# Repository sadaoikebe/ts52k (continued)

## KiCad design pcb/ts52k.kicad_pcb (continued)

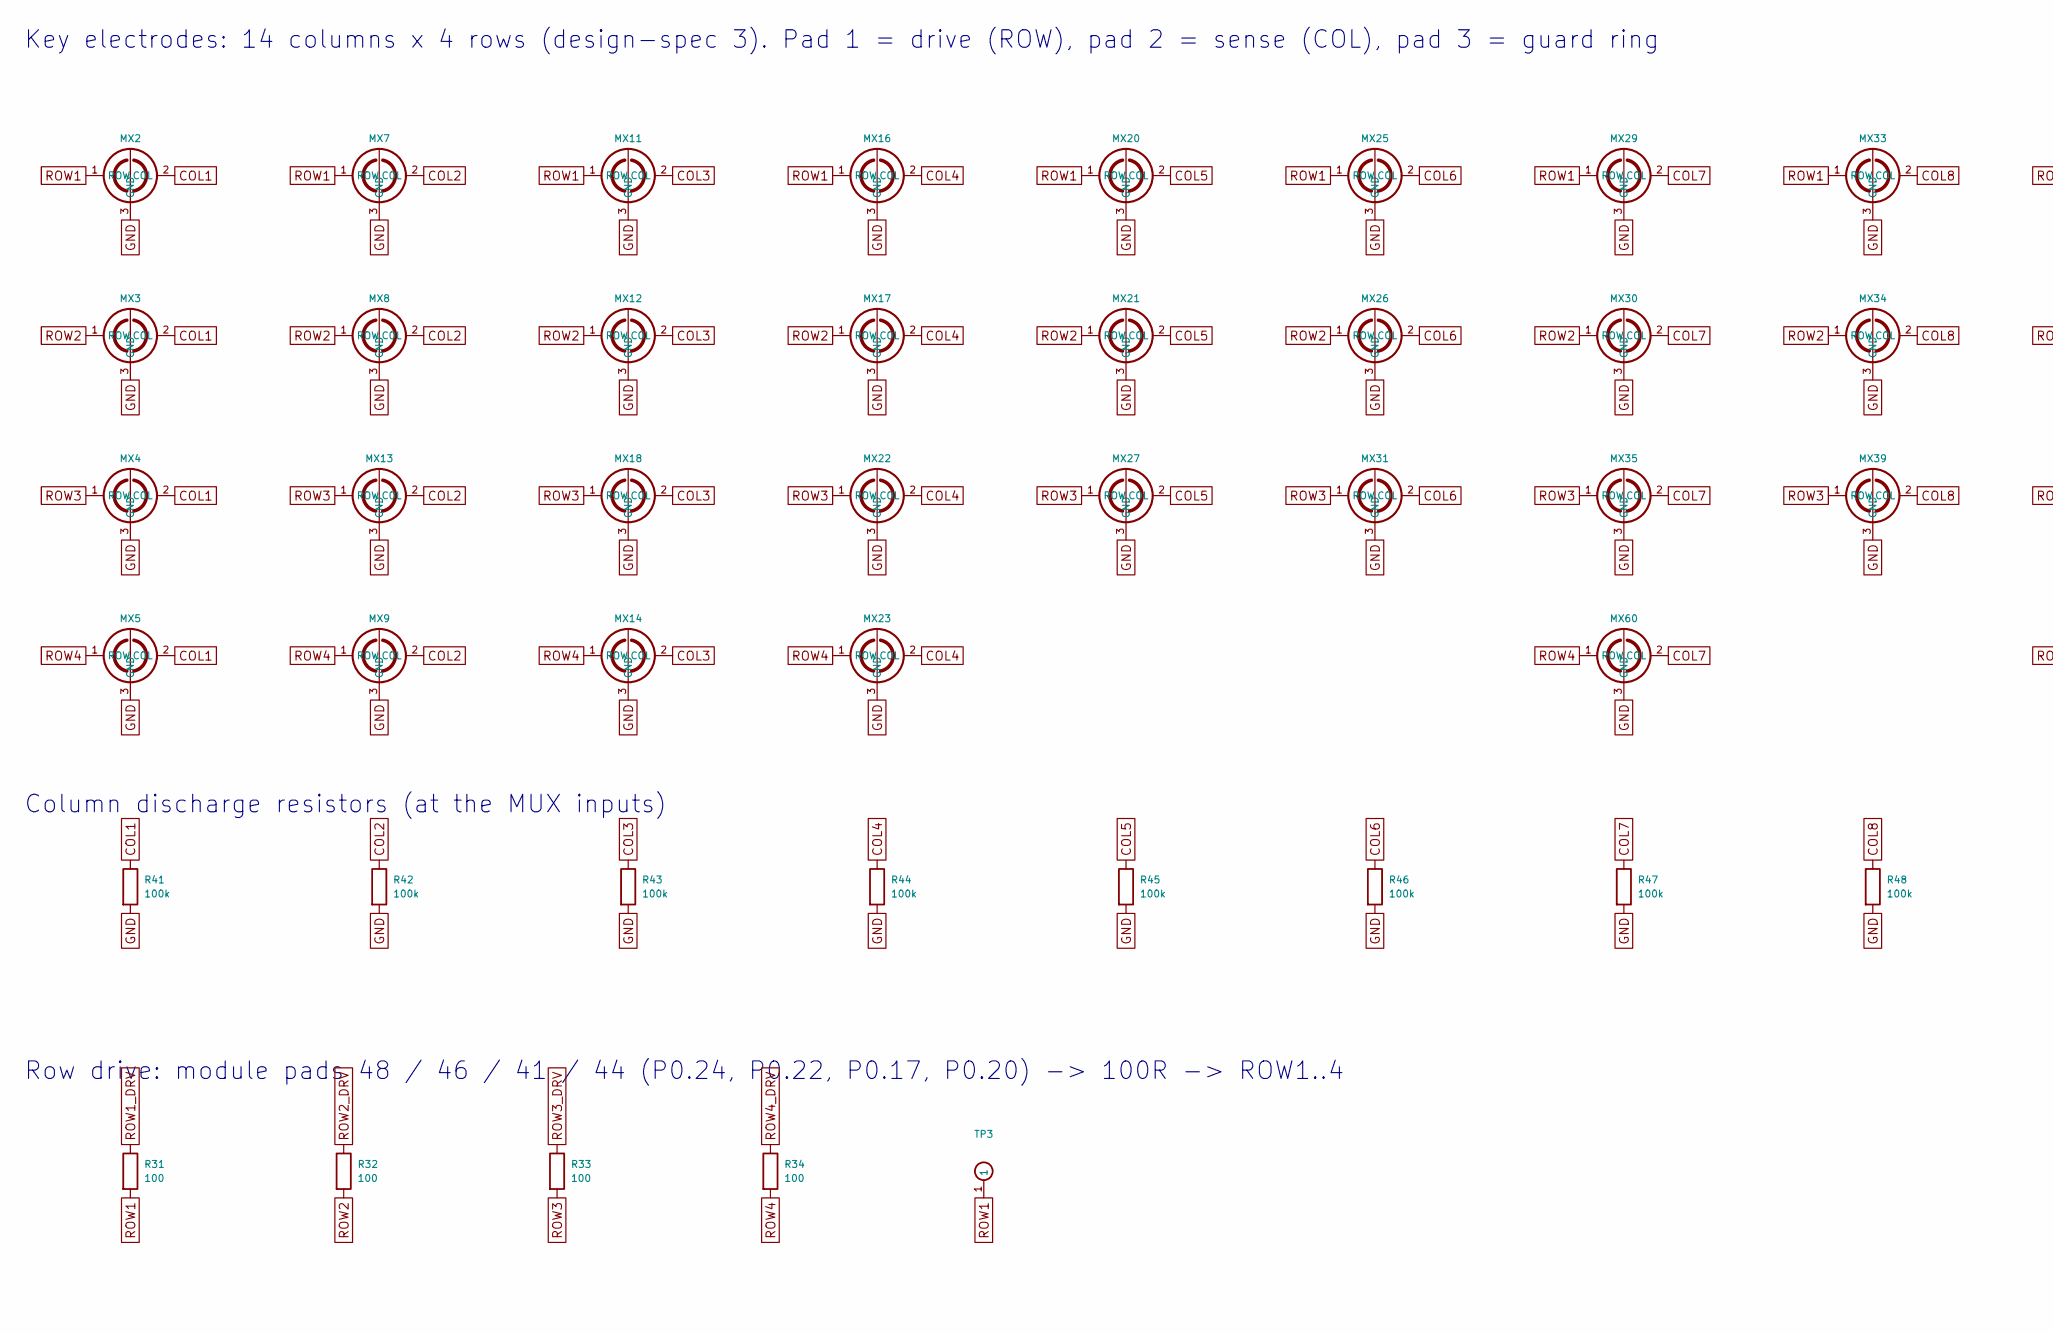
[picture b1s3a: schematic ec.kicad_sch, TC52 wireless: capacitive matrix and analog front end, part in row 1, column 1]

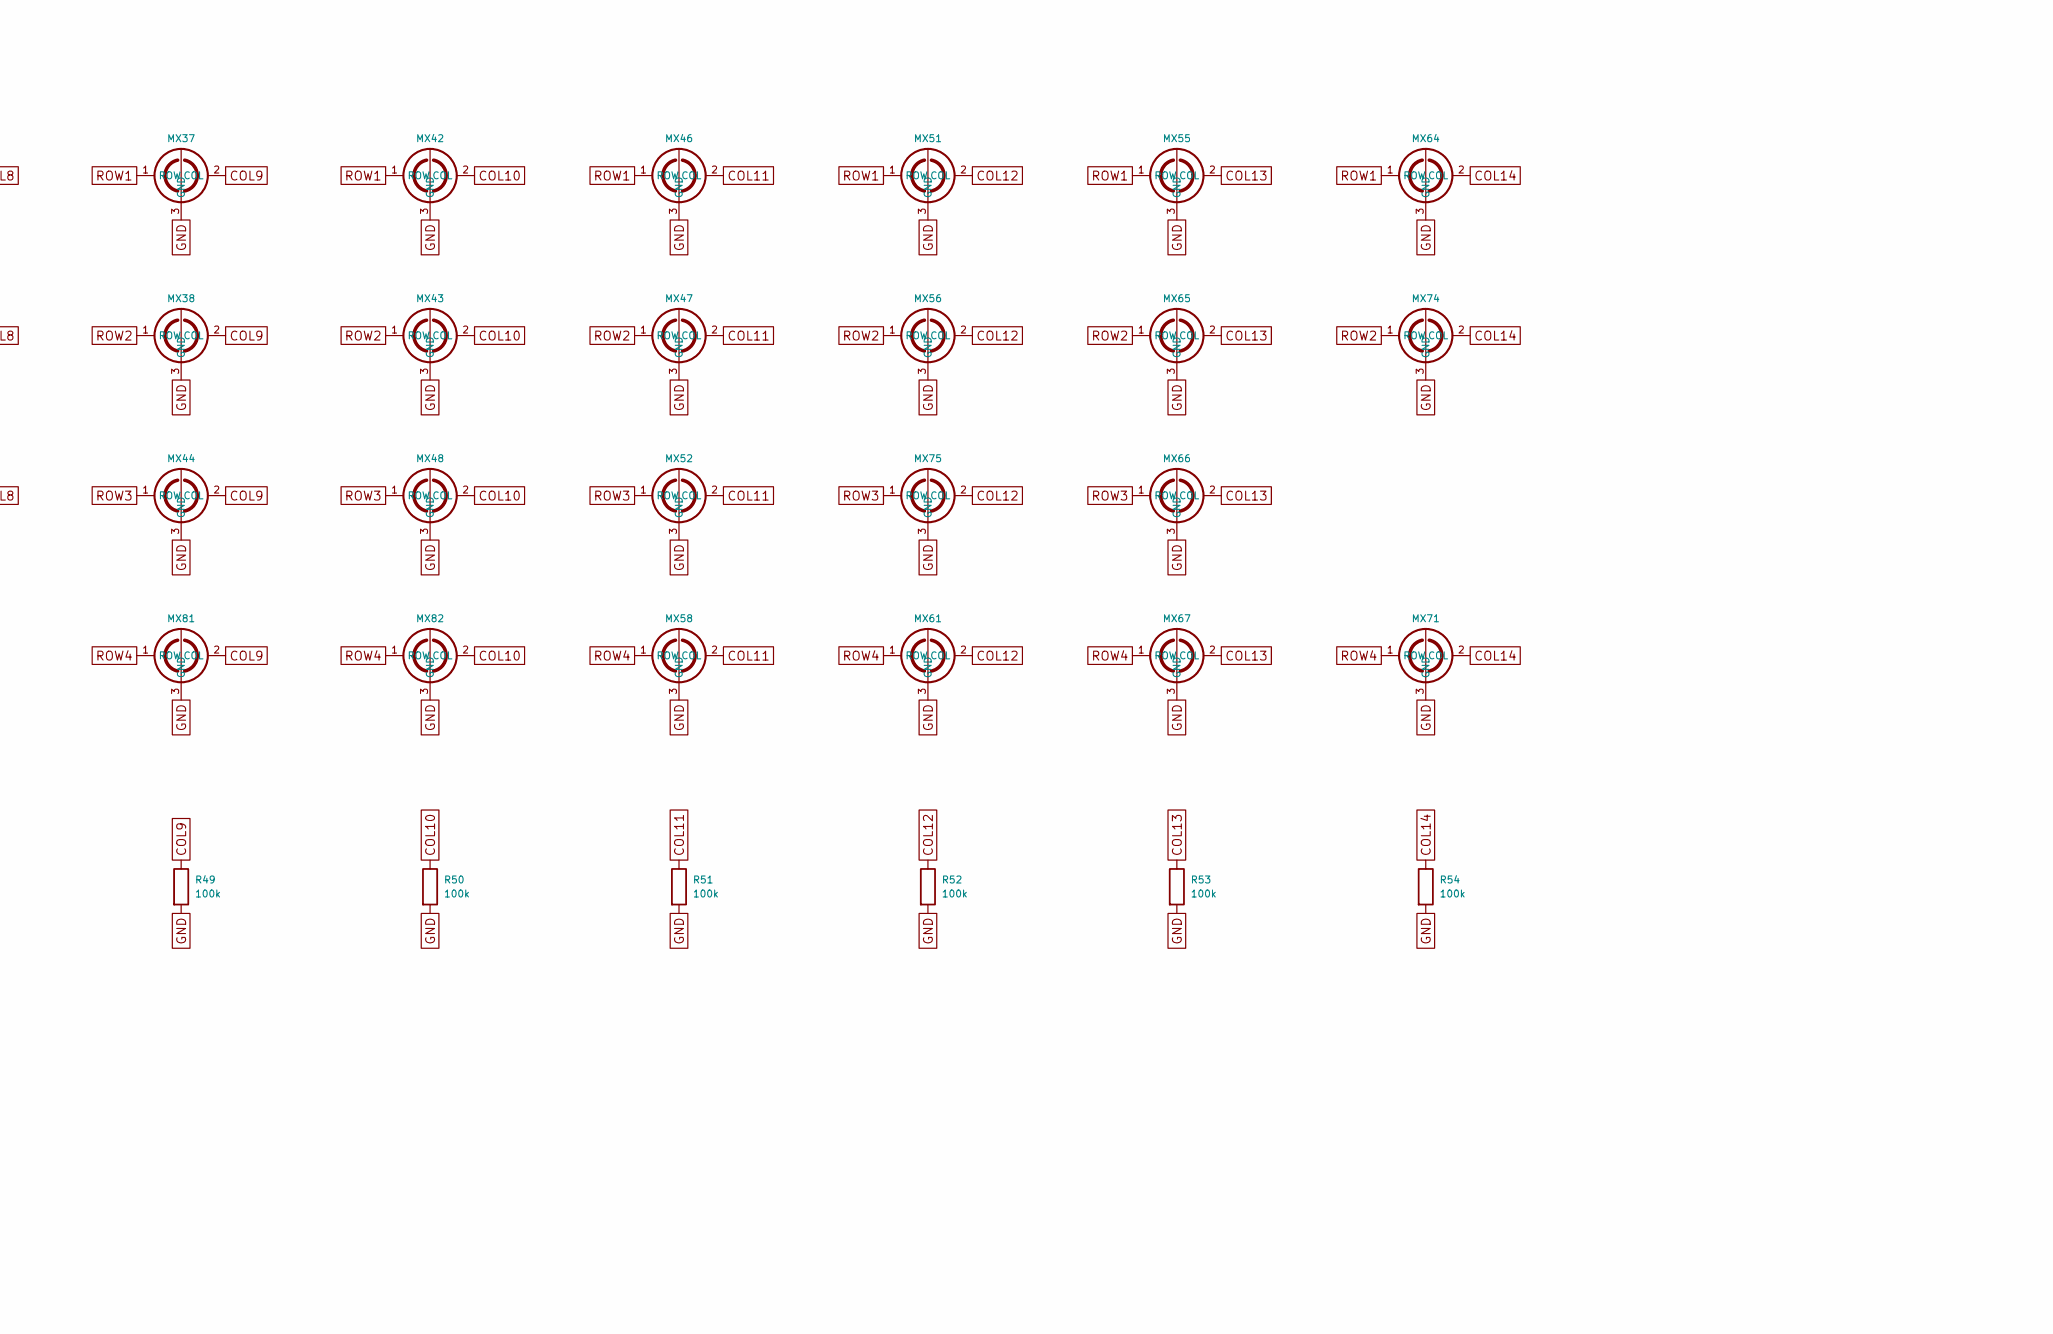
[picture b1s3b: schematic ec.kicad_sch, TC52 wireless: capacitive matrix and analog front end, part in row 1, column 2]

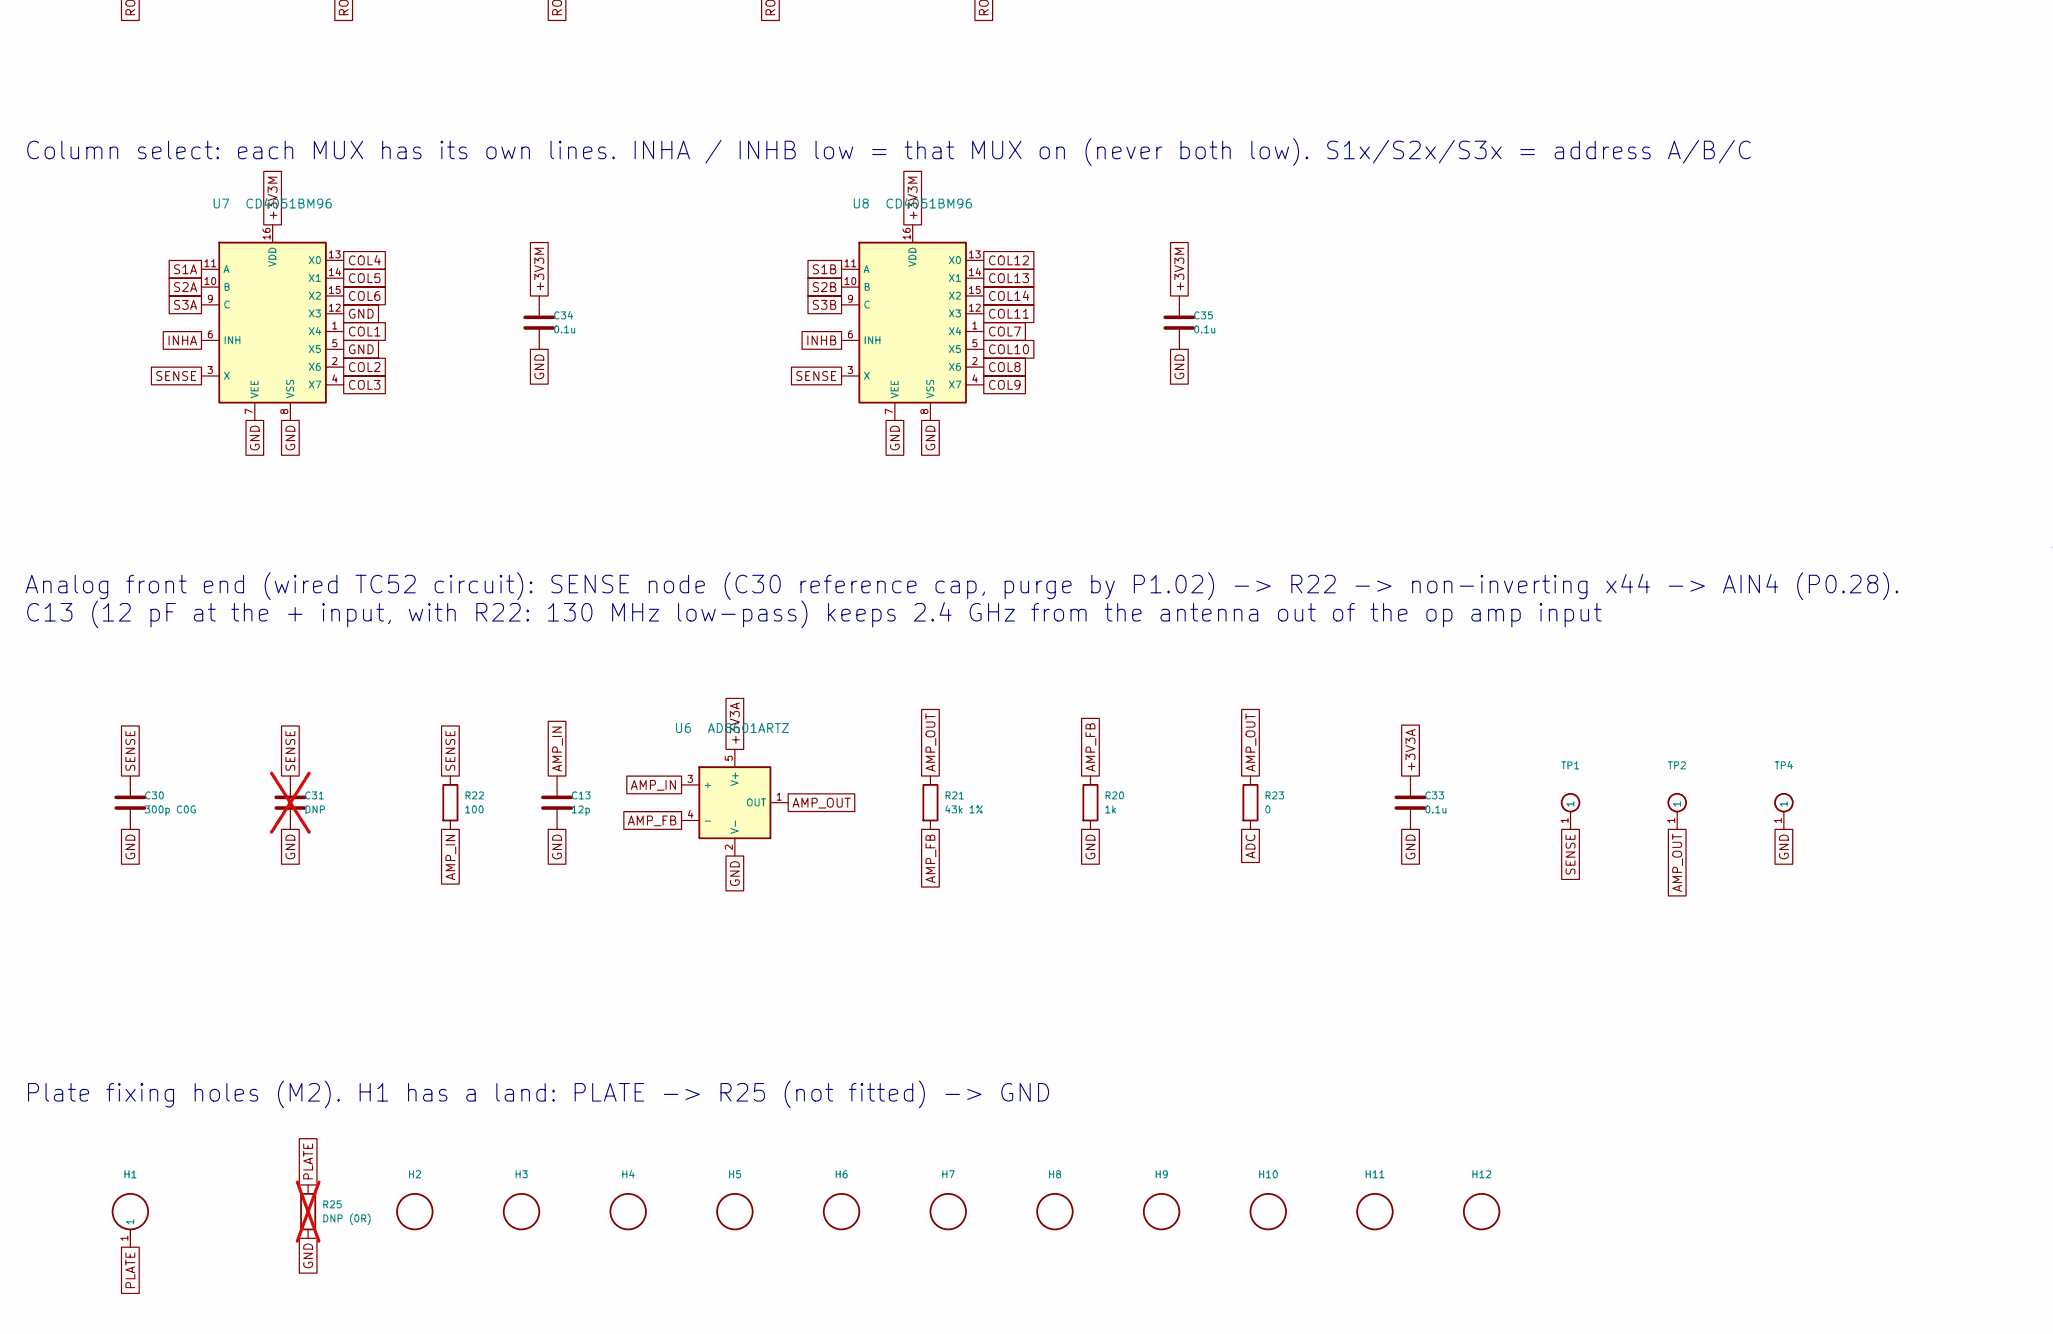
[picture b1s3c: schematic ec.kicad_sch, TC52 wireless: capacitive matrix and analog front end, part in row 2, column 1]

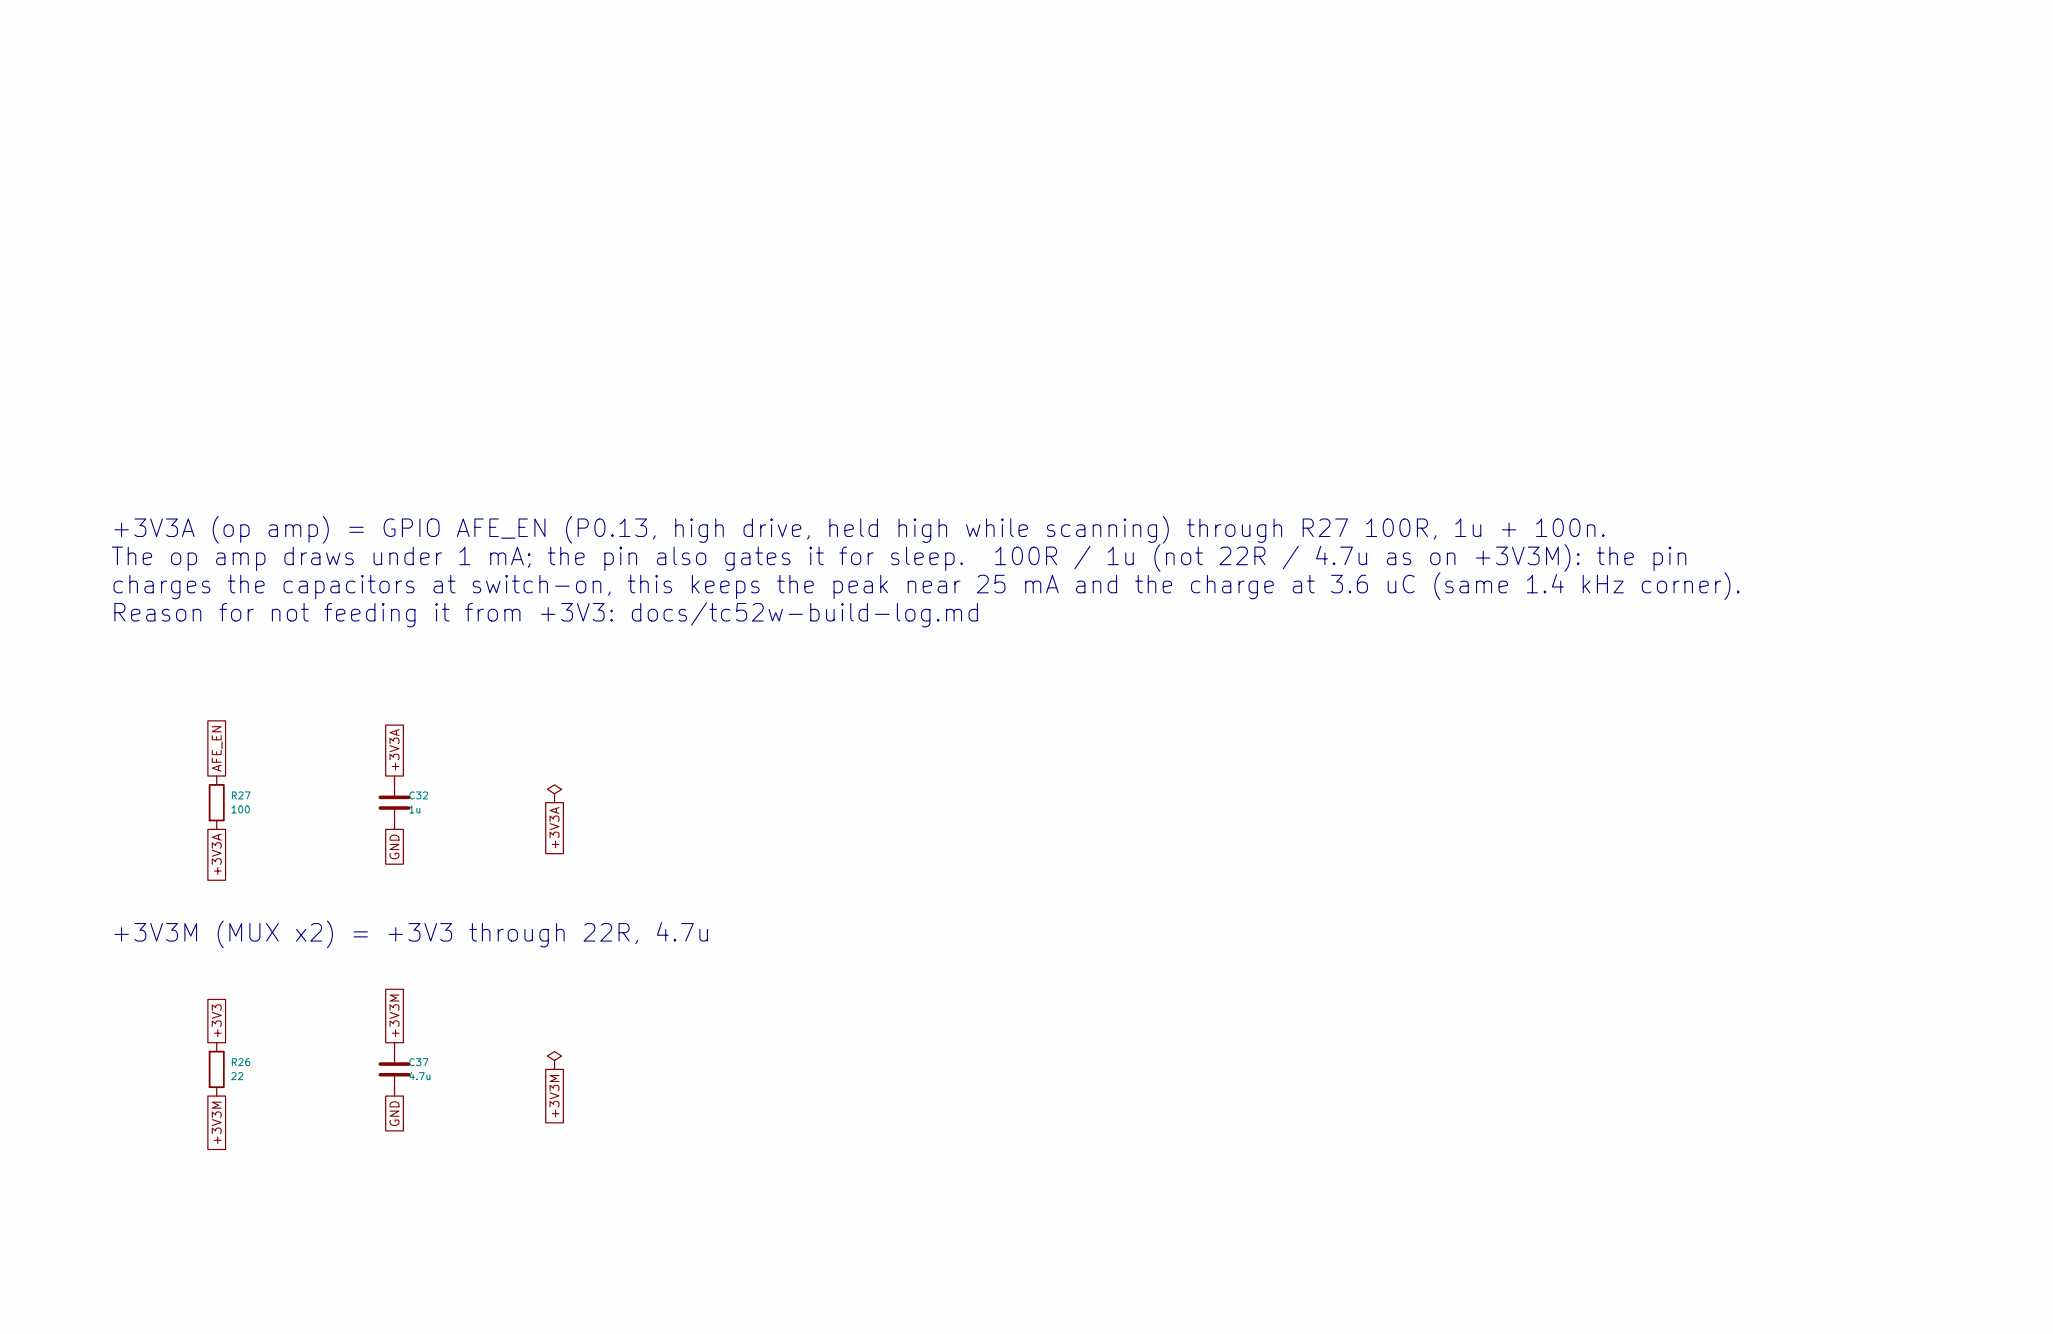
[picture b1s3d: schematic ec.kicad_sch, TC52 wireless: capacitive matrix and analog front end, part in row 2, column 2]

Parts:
C13: 12p; C_0402_1005Metric; MPN 0402CG120J500NT; LCSC C1547
C30: 300p C0G; C_0603_1608Metric; MPN 0603CG301J500NT; LCSC C52152
C31: DNP; C_0603_1608Metric; not fitted
C32: 1u; C_0402_1005Metric; MPN CL05A105KA5NQNC; LCSC C52923
C33, C34, C35: 0.1u; C_0402_1005Metric; MPN CL05B104KO5NNNC; LCSC C1525
C37: 4.7u; C_0402_1005Metric; MPN CL05A475MP5NRNC; LCSC C23733
H1: PLATE; Hole_M2_Pad
H2, H3, H4, H5, H6, H7, H8, H9, H10, H11, H12: M2; MountingHole_2.1mm
MX2, MX3, MX4, MX5, MX7, MX8, MX9, MX11, MX12, MX13, MX14, MX16, MX17, MX18, MX20, MX21, MX22, MX23, MX25, MX26, MX27, MX29, MX30, MX31, MX33, MX34, MX35, MX37, MX38, MX39, MX42, MX43, MX44, MX46, MX47, MX48, MX51, MX52, MX55, MX56, MX58, MX60, MX61, MX64, MX65, MX66, MX67, MX71, MX75, MX81, MX82: ECS_PAD; ecs_pad
MX74: ECS_PAD; ecs_pad_edge
R20: 1k; R_0402_1005Metric; MPN 0402WGF1001TCE; LCSC C11702
R21: 43k 1%; R_0402_1005Metric; MPN CR0402F43K0Q10Z; LCSC C881384
R22, R27, R31, R32, R33, R34: 100; R_0402_1005Metric; MPN 0402WGF1000TCE; LCSC C25076
R23: 0; R_0402_1005Metric; MPN 0402WGF0000TCE; LCSC C17168
R25: DNP (0R); R_0402_1005Metric; not fitted
R26: 22; R_0402_1005Metric; MPN 0402WGF220JTCE; LCSC C25092
R41, R42, R43, R44, R45, R46, R47, R48, R49, R50, R51, R52, R53, R54: 100k; R_0402_1005Metric; MPN 0402WGF1003TCE; LCSC C25741
TP1: SENSE; TestPoint_Pad_D1.0mm
TP2: ADC; TestPoint_Pad_D1.0mm
TP3: ROW1; TestPoint_Pad_D1.0mm
TP4: GND; TestPoint_Pad_D1.0mm
U6: AD8601ARTZ; SOT-23-5; MPN AD8601ARTZ-REEL7; LCSC C41249
U7, U8: CD4051BM96; SOIC-16_3.9x9.9mm_P1.27mm; MPN CD4051BM96; LCSC C21379

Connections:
+3V3: R26.1; also elsewhere on the board
+3V3A: C32.1, C33.1, R27.2, U6.5 (V+)
+3V3M: C34.1, C35.1, C37.1, R26.2, U7.16 (VDD), U8.16 (VDD)
ADC: R23.2; also elsewhere on the board
AFE_EN: R27.1; also elsewhere on the board
AMP_FB: R20.1, R21.2, U6.4 (-)
AMP_IN: C13.1, R22.2, U6.3 (+)
AMP_OUT: R21.1, R23.1, TP2.1, U6.1 (OUT)
COL1: MX2.2 (COL), MX3.2 (COL), MX4.2 (COL), MX5.2 (COL), R41.1, U7.1 (X4)
COL2: MX7.2 (COL), MX8.2 (COL), MX9.2 (COL), MX13.2 (COL), R42.1, U7.2 (X6)
COL3: MX11.2 (COL), MX12.2 (COL), MX14.2 (COL), MX18.2 (COL), R43.1, U7.4 (X7)
COL4: MX16.2 (COL), MX17.2 (COL), MX22.2 (COL), MX23.2 (COL), R44.1, U7.13 (X0)
COL5: MX20.2 (COL), MX21.2 (COL), MX27.2 (COL), R45.1, U7.14 (X1)
COL6: MX25.2 (COL), MX26.2 (COL), MX31.2 (COL), R46.1, U7.15 (X2)
COL7: MX29.2 (COL), MX30.2 (COL), MX35.2 (COL), MX60.2 (COL), R47.1, U8.1 (X4)
COL8: MX33.2 (COL), MX34.2 (COL), MX39.2 (COL), R48.1, U8.2 (X6)
COL9: MX37.2 (COL), MX38.2 (COL), MX44.2 (COL), MX81.2 (COL), R49.1, U8.4 (X7)
COL10: MX42.2 (COL), MX43.2 (COL), MX48.2 (COL), MX82.2 (COL), R50.1, U8.5 (X5)
COL11: MX46.2 (COL), MX47.2 (COL), MX52.2 (COL), MX58.2 (COL), R51.1, U8.12 (X3)
COL12: MX51.2 (COL), MX56.2 (COL), MX61.2 (COL), MX75.2 (COL), R52.1, U8.13 (X0)
COL13: MX55.2 (COL), MX65.2 (COL), MX66.2 (COL), MX67.2 (COL), R53.1, U8.14 (X1)
COL14: MX64.2 (COL), MX71.2 (COL), MX74.2 (COL), R54.1, U8.15 (X2)
GND: C13.2, C30.2, C31.2, C32.2, C33.2, C34.2, C35.2, C37.2, MX2.3 (GND), MX3.3 (GND), MX4.3 (GND), MX5.3 (GND), MX7.3 (GND), MX8.3 (GND), MX9.3 (GND), MX11.3 (GND), MX12.3 (GND), MX13.3 (GND), MX14.3 (GND), MX16.3 (GND), MX17.3 (GND), MX18.3 (GND), MX20.3 (GND), MX21.3 (GND), MX22.3 (GND), MX23.3 (GND), MX25.3 (GND), MX26.3 (GND), MX27.3 (GND), MX29.3 (GND), MX30.3 (GND), MX31.3 (GND), MX33.3 (GND), MX34.3 (GND), MX35.3 (GND), MX37.3 (GND), MX38.3 (GND), MX39.3 (GND), MX42.3 (GND), MX43.3 (GND), MX44.3 (GND), MX46.3 (GND), MX47.3 (GND), MX48.3 (GND), MX51.3 (GND), MX52.3 (GND), MX55.3 (GND), MX56.3 (GND), MX58.3 (GND), MX60.3 (GND), MX61.3 (GND), MX64.3 (GND), MX65.3 (GND), MX66.3 (GND), MX67.3 (GND), MX71.3 (GND), MX74.3 (GND), MX75.3 (GND), MX81.3 (GND), MX82.3 (GND), R20.2, R25.2, R41.2, R42.2, R43.2, R44.2, R45.2, R46.2, R47.2, R48.2, R49.2, R50.2, R51.2, R52.2, R53.2, R54.2, TP4.1, U6.2 (V-), U7.5 (X5), U7.7 (VEE), U7.8 (VSS), U7.12 (X3), U8.7 (VEE), U8.8 (VSS); also elsewhere on the board
INHA: U7.6 (INH); also elsewhere on the board
INHB: U8.6 (INH); also elsewhere on the board
PLATE: H1.1, R25.1
ROW1: MX2.1 (ROW), MX7.1 (ROW), MX11.1 (ROW), MX16.1 (ROW), MX20.1 (ROW), MX25.1 (ROW), MX29.1 (ROW), MX33.1 (ROW), MX37.1 (ROW), MX42.1 (ROW), MX46.1 (ROW), MX51.1 (ROW), MX55.1 (ROW), MX64.1 (ROW), R31.2, TP3.1
ROW1_DRV: R31.1; also elsewhere on the board
ROW2: MX3.1 (ROW), MX8.1 (ROW), MX12.1 (ROW), MX17.1 (ROW), MX21.1 (ROW), MX26.1 (ROW), MX30.1 (ROW), MX34.1 (ROW), MX38.1 (ROW), MX43.1 (ROW), MX47.1 (ROW), MX56.1 (ROW), MX65.1 (ROW), MX74.1 (ROW), R32.2
ROW2_DRV: R32.1; also elsewhere on the board
ROW3: MX4.1 (ROW), MX13.1 (ROW), MX18.1 (ROW), MX22.1 (ROW), MX27.1 (ROW), MX31.1 (ROW), MX35.1 (ROW), MX39.1 (ROW), MX44.1 (ROW), MX48.1 (ROW), MX52.1 (ROW), MX66.1 (ROW), MX75.1 (ROW), R33.2
ROW3_DRV: R33.1; also elsewhere on the board
ROW4: MX5.1 (ROW), MX9.1 (ROW), MX14.1 (ROW), MX23.1 (ROW), MX58.1 (ROW), MX60.1 (ROW), MX61.1 (ROW), MX67.1 (ROW), MX71.1 (ROW), MX81.1 (ROW), MX82.1 (ROW), R34.2
ROW4_DRV: R34.1; also elsewhere on the board
S1A: U7.11 (A); also elsewhere on the board
S1B: U8.11 (A); also elsewhere on the board
S2A: U7.10 (B); also elsewhere on the board
S2B: U8.10 (B); also elsewhere on the board
S3A: U7.9 (C); also elsewhere on the board
S3B: U8.9 (C); also elsewhere on the board
SENSE: C30.1, C31.1, R22.1, TP1.1, U7.3 (X), U8.3 (X); also elsewhere on the board

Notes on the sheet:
Key electrodes: 14 columns x 4 rows (design-spec 3). Pad 1 = drive (ROW), pad 2 = sense (COL), pad 3 = guard ring
Column discharge resistors (at the MUX inputs)
Row drive: module pads 48 / 46 / 41 / 44 (P0.24, P0.22, P0.17, P0.20) -> 100R -> ROW1..4
Column select: each MUX has its own lines. INHA / INHB low = that MUX on (never both low). S1x/S2x/S3x = address A/B/C
Analog front end (wired TC52 circuit): SENSE node (C30 reference cap, purge by P1.02) -> R22 -> non-inverting x44 -> AIN4 (P0.28). C13 (12 pF at the + input, with R22: 130 MHz low-pass) keeps 2.4 GHz from the antenna out of the op amp input
+3V3A (op amp) = GPIO AFE_EN (P0.13, high drive, held high while scanning) through R27 100R, 1u + 100n. The op amp draws under 1 mA; the pin also gates it for sleep. 100R / 1u (not 22R / 4.7u as on +3V3M): the pin charges the capacitors at switch-on, this keeps the peak near 25 mA and the charge at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
+3V3M (MUX x2) = +3V3 through 22R, 4.7u
Plate fixing holes (M2). H1 has a land: PLATE -> R25 (not fitted) -> GND

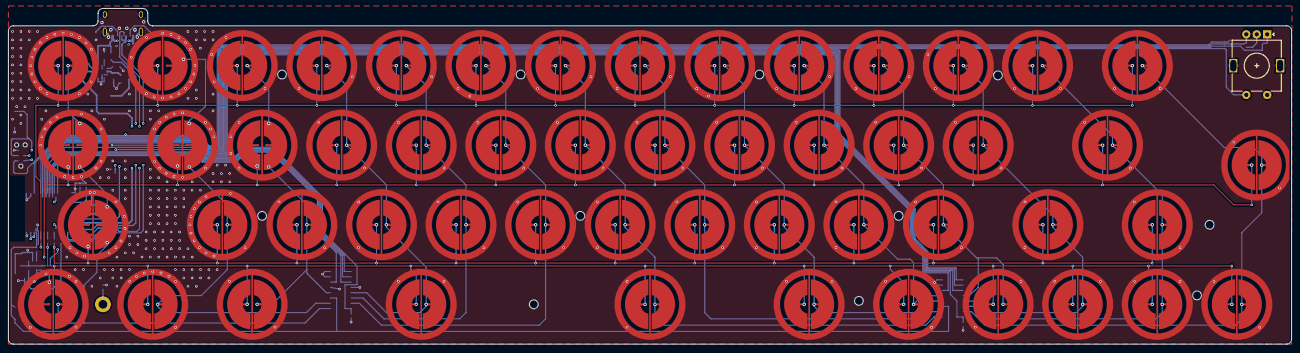
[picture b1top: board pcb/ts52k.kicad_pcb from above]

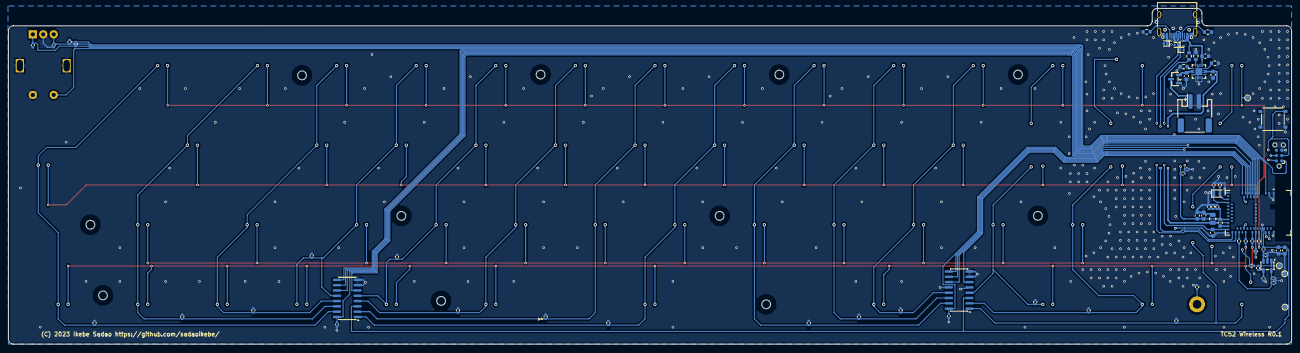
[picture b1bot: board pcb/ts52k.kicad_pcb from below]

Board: 4 copper layers, 307.2 x 80.4 mm, 139 parts (74 on the bottom side), 62 nets.

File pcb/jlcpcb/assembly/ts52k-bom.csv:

Comment,Designator,Footprint,LCSC Part #
1u,"C1,C7",ts52k:C_0603_1608Metric,C15849
4.7u,"C2,C3,C5,C6",ts52k:C_0603_1608Metric,C19666
10u,C4,ts52k:C_0805_2012Metric,C15850
0.1u,"C8,C9,C10,C19,C20,C33,C34,C35",Capacitor_SMD:C_0402_1005Metric,C1525
12p,"C11,C12,C13",Capacitor_SMD:C_0402_1005Metric,C1547
300p C0G,C30,Capacitor_SMD:C_0603_1608Metric,C52152
1u,C32,Capacitor_SMD:C_0402_1005Metric,C52923
4.7u,C37,Capacitor_SMD:C_0402_1005Metric,C23733
H5VU10U,"D89,D90,D91",Diode_SMD:D_SOD-882D,C22395519
TYPE-C-31-M-12,J1,ts52k:USB_C_Receptacle_HRO_TYPE-C-31-M-12,C165948
JST PH 2-pin,J3,ts52k:JST_PH_S2B-PH-SM4-TB_1x02-1MP_P2.00mm_Horizontal,C295747
10uH,L1,ts52k:L_0603_1608Metric,C713281
AO3401A,Q1,ts52k:SOT-23,C15127
8.2k,R1,ts52k:R_0603_1608Metric,C25981
1.5k,R2,ts52k:R_0603_1608Metric,C22843
10k,R3,ts52k:R_0603_1608Metric,C25804
2.2,R4,ts52k:R_0603_1608Metric,C22939
5.1k,"R5,R6",ts52k:R_0603_1608Metric,C23186
10k,"R15,R16",Resistor_SMD:R_0402_1005Metric,C25744
1k,R20,Resistor_SMD:R_0402_1005Metric,C11702
43k 1%,R21,Resistor_SMD:R_0402_1005Metric,C881384
100,"R22,R27,R31,R32,R33,R34",Resistor_SMD:R_0402_1005Metric,C25076
0,R23,Resistor_SMD:R_0402_1005Metric,C17168
22,R26,Resistor_SMD:R_0402_1005Metric,C25092
100k,"R41,R42,R43,R44,R45,R46,R47,R48,R49,R50,R51,R52,R53,R54",Resistor_SMD:R_0402_1005Metric,C25741
RESET,SW1,ts52k:SW_Tactile_XKB_TS-1187A_5.1x5.1mm,C318884
MDBT50Q-1MV2,U5,ts52k:Raytac_MDBT50Q,C5118826
AD8601ARTZ,U6,Package_TO_SOT_SMD:SOT-23-5,C41249
CD4051BM96,"U7,U8",Package_SO:SOIC-16_3.9x9.9mm_P1.27mm,C21379
BQ24072RGTR,U9,ts52k:VQFN-16-1EP_3x3mm_P0.5mm_EP1.68x1.68mm,C140288
32.768kHz,X1,ts52k:Crystal_Epson_FC-12M_2.05x1.2mm,C96341

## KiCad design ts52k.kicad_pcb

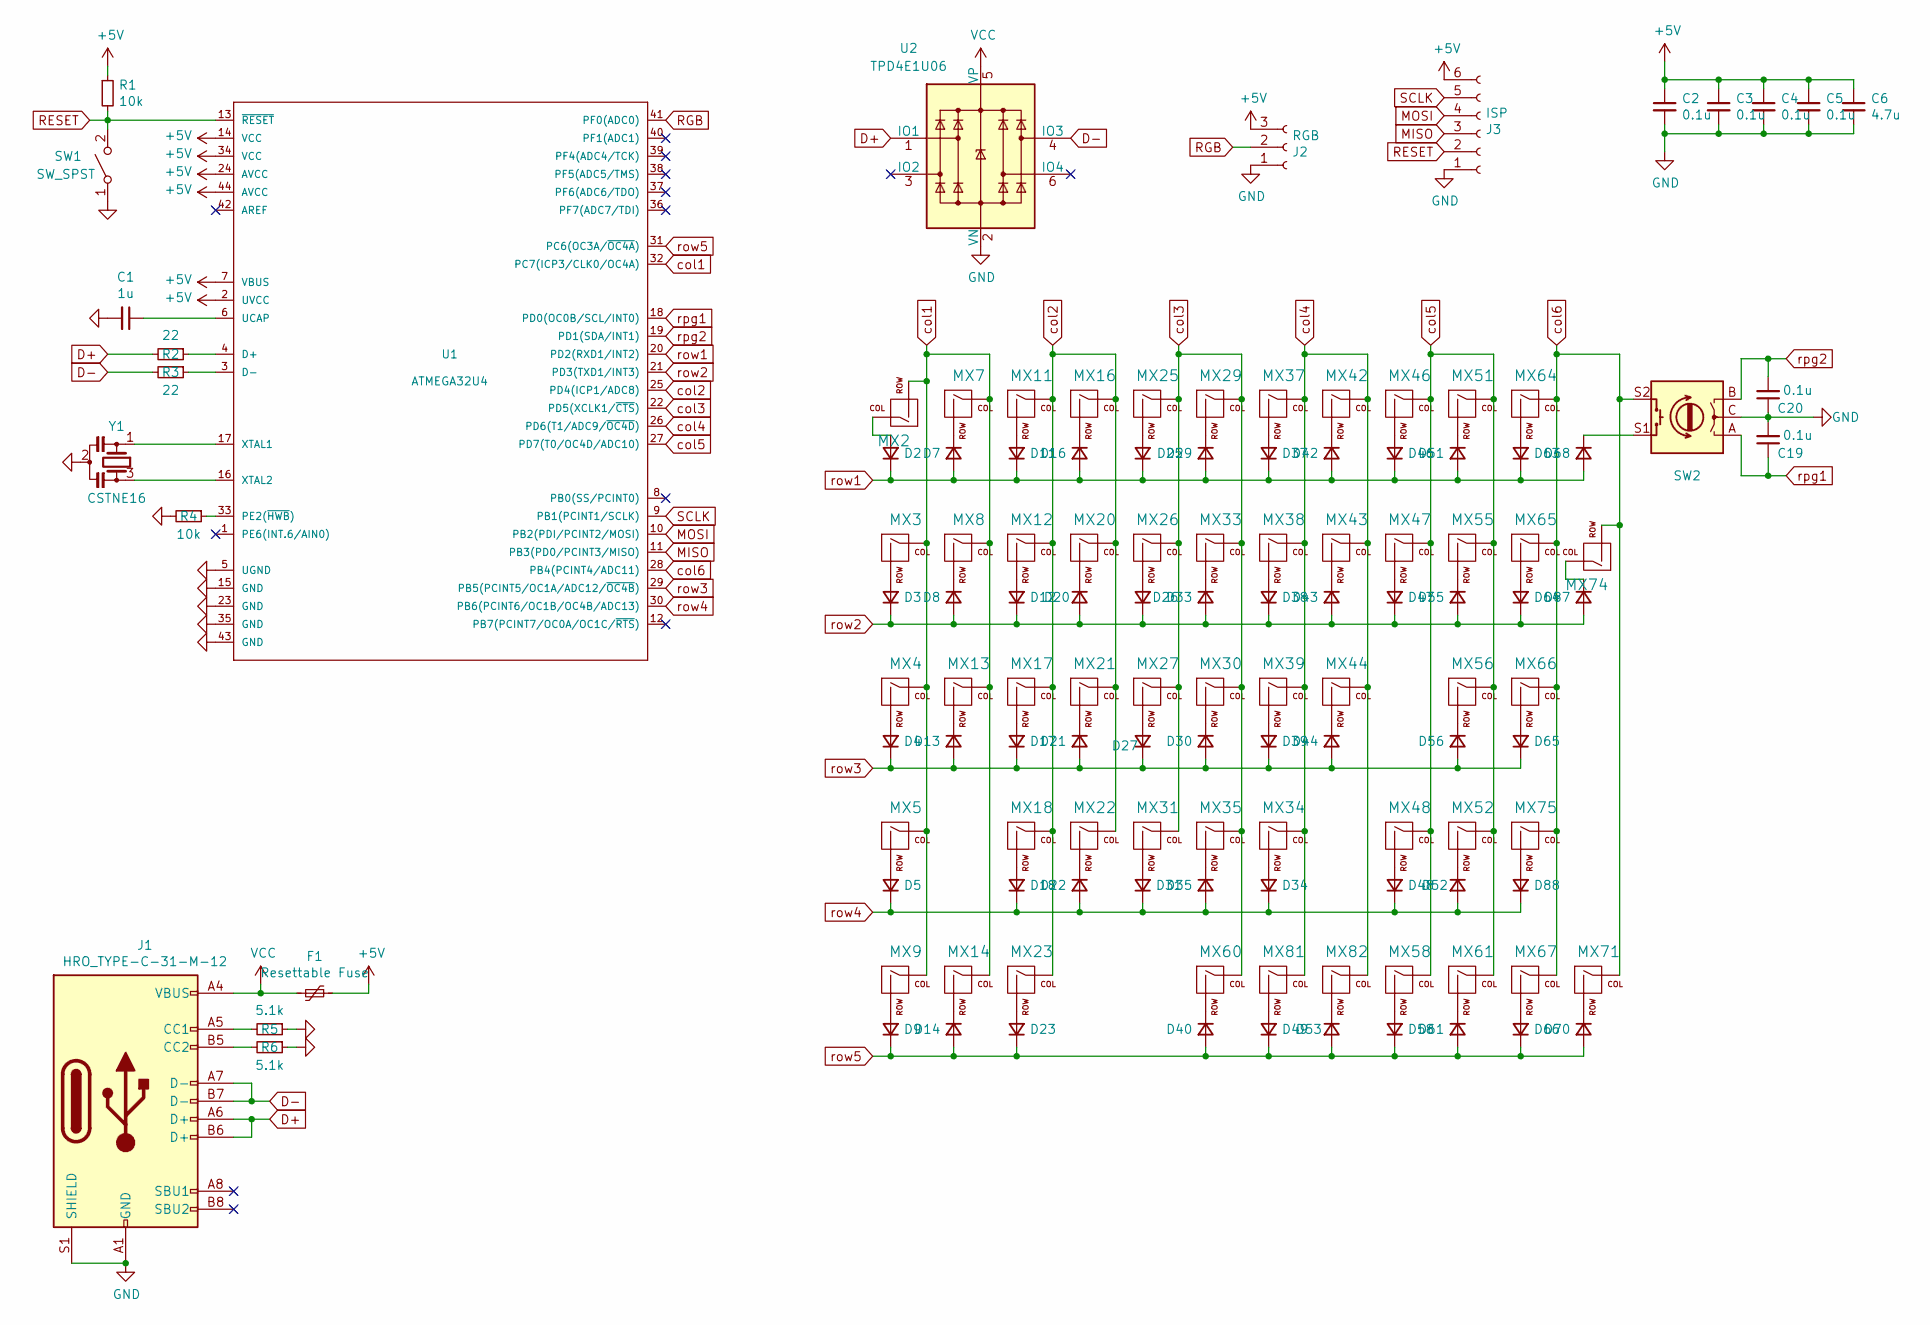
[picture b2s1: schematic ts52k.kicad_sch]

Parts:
C1: 1u; C_0603_1608Metric; LCSC C5673
C2, C3, C4, C5, C19, C20: 0.1u; C_0402_1005Metric; LCSC C60474
C6: 4.7u; C_0603_1608Metric; LCSC C1705
D2, D3, D4, D5, D7, D8, D9, D11, D12, D13, D14, D16, D17, D18, D20, D21, D22, D23, D25, D26, D27, D29, D30, D31, D33, D34, D35, D37, D38, D39, D40, D42, D43, D44, D46, D47, D48, D49, D51, D52, D53, D55, D56, D58, D61, D63, D64, D65, D66, D68, D70, D87, D88: D; D_SOD-123; LCSC C84367
F1: Resettable Fuse; Fuse_0805_2012Metric; MPN SMD0805B050TF; LCSC C269104
J1: HRO_TYPE-C-31-M-12; USB_C_Receptacle_HRO_TYPE-C-31-M-12; LCSC C165948
J2: RGB; PinHeader_1x03_P2.00mm_Vertical
J3: ISP; PinHeader_1x06_P1.27mm_Vertical
MX2, MX64: MX-NoLED; MXOnly-1.5U-NoLED
MX3, MX75: MX-NoLED; MXOnly-1.75U-NoLED
MX4, MX65: MX-NoLED; MXOnly-2.25U-NoLED
MX5, MX9, MX14, MX81, MX82: MX-NoLED; MXOnly-1.25U-NoLED
MX7, MX8, MX11, MX12, MX13, MX16, MX17, MX18, MX20, MX21, MX22, MX25, MX26, MX27, MX29, MX30, MX31, MX33, MX34, MX35, MX37, MX38, MX39, MX42, MX43, MX44, MX46, MX47, MX48, MX51, MX52, MX55, MX56, MX58, MX61, MX66, MX67, MX71, MX74: MX-NoLED; MXOnly-1U-NoLED
MX23: MX-NoLED; MXOnly-3U-ReversedStabilizers-NoLED
MX60: MX-NoLED; MXOnly-2.75U-ReversedStabilizers-NoLED
R1, R4: 10k; R_0805_2012Metric; LCSC C269742
R2, R3: 22; R_0603_1608Metric; LCSC C269708
R5, R6: 5.1k; R_0603_1608Metric; LCSC C269716
SW1: SW_SPST; SW_SPST_TL3342; LCSC C780528
SW2: RotaryEncoder_Switch; RotaryEncoder_Alps_EC11E-Switch_Vertical_H20mm
U1: ATMEGA32U4; QFN-44-1EP_7x7mm_P0.5mm_EP5.2x5.2mm; MPN ATMEGA32U4; LCSC C44854
U2: TPD4E1U06; SOT-363_SC-70-6; MPN TPD4E1U06DBV; LCSC C194628
Y1: CSTNE16; Resonator_SMD_muRata_CSTxExxV-3Pin_3.0x1.1mm; MPN CSTNE16M0V530000R0; LCSC C341521

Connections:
+5V: C2.1, C3.1, C4.1, C5.1, C6.1, F1.1, J2.3, J3.6, R1.1, U1.2 (UVCC), U1.7 (VBUS), U1.14 (VCC), U1.24 (AVCC), U1.34 (VCC), U1.44 (AVCC)
D+: J1.A6 (D+), J1.B6 (D+), R2.2, U2.1 (IO1)
D-: J1.A7 (D-), J1.B7 (D-), R3.2, U2.4 (IO3)
GND: C1.2, C2.2, C3.2, C4.2, C5.2, C6.2, C19.2, C20.1, J1.A1 (GND), J1.A12 (GND), J1.B1 (GND), J1.B12 (GND), J1.S1 (SHIELD), J2.1, J3.1, R4.2, R5.1, R6.1, SW1.1 (A), SW2.C, U1.5 (UGND), U1.15 (GND), U1.23 (GND), U1.35 (GND), U1.43 (GND), U2.2 (VN), Y1.2
MISO: J3.3, U1.11 (PB3(PD0/PCINT3/MISO))
MOSI: J3.4, U1.10 (PB2(PDI/PCINT2/MOSI))
unnamed: C1.1, U1.6 (UCAP)
unnamed: D2.2 (A), MX2.1 (COL)
unnamed: D3.2 (A), MX3.2 (ROW)
unnamed: D4.2 (A), MX4.2 (ROW)
unnamed: D5.2 (A), MX5.2 (ROW)
unnamed: D7.1 (K), MX7.2 (ROW)
unnamed: D8.1 (K), MX8.2 (ROW)
unnamed: D9.2 (A), MX9.2 (ROW)
unnamed: D11.2 (A), MX11.2 (ROW)
unnamed: D12.2 (A), MX12.2 (ROW)
unnamed: D13.1 (K), MX13.2 (ROW)
unnamed: D14.1 (K), MX14.2 (ROW)
unnamed: D16.1 (K), MX16.2 (ROW)
unnamed: D17.2 (A), MX17.2 (ROW)
unnamed: D18.2 (A), MX18.2 (ROW)
unnamed: D20.1 (K), MX20.2 (ROW)
unnamed: D21.1 (K), MX21.2 (ROW)
unnamed: D22.1 (K), MX22.2 (ROW)
unnamed: D23.2 (A), MX23.2 (ROW)
unnamed: D25.2 (A), MX25.2 (ROW)
unnamed: D26.2 (A), MX26.2 (ROW)
unnamed: D27.2 (A), MX27.2 (ROW)
unnamed: D29.1 (K), MX29.2 (ROW)
unnamed: D30.1 (K), MX30.2 (ROW)
unnamed: D31.2 (A), MX31.2 (ROW)
unnamed: D33.1 (K), MX33.2 (ROW)
unnamed: D34.2 (A), MX34.2 (ROW)
unnamed: D35.1 (K), MX35.2 (ROW)
unnamed: D37.2 (A), MX37.2 (ROW)
unnamed: D38.2 (A), MX38.2 (ROW)
unnamed: D39.2 (A), MX39.2 (ROW)
unnamed: D40.1 (K), MX60.2 (ROW)
unnamed: D42.1 (K), MX42.2 (ROW)
unnamed: D43.1 (K), MX43.2 (ROW)
unnamed: D44.1 (K), MX44.2 (ROW)
unnamed: D46.2 (A), MX46.2 (ROW)
unnamed: D47.2 (A), MX47.2 (ROW)
unnamed: D48.2 (A), MX48.2 (ROW)
unnamed: D49.2 (A), MX81.2 (ROW)
unnamed: D51.1 (K), MX51.2 (ROW)
unnamed: D52.1 (K), MX52.2 (ROW)
unnamed: D53.1 (K), MX82.2 (ROW)
unnamed: D55.1 (K), MX55.2 (ROW)
unnamed: D56.1 (K), MX56.2 (ROW)
unnamed: D58.2 (A), MX58.2 (ROW)
unnamed: D61.1 (K), MX61.2 (ROW)
unnamed: D63.2 (A), MX64.2 (ROW)
unnamed: D64.2 (A), MX65.2 (ROW)
unnamed: D65.2 (A), MX66.2 (ROW)
unnamed: D66.2 (A), MX67.2 (ROW)
unnamed: D68.1 (K), SW2.S1
unnamed: D70.1 (K), MX71.2 (ROW)
unnamed: D87.1 (K), MX74.1 (COL)
unnamed: D88.2 (A), MX75.2 (ROW)
unnamed: J1.A5 (CC1), R5.2
unnamed: J1.B5 (CC2), R6.2
unnamed: R2.1, U1.4 (D+)
unnamed: R3.1, U1.3 (D-)
unnamed: R4.1, U1.33 (PE2(~HWB))
unnamed: U1.16 (XTAL2), Y1.3
unnamed: U1.17 (XTAL1), Y1.1
RESET: J3.2, R1.2, SW1.2 (B), U1.13 (~RESET)
RGB: J2.2, U1.41 (PF0(ADC0))
SCLK: J3.5, U1.9 (PB1(PCINT1/SCLK))
VCC: F1.2, J1.A4 (VBUS), J1.A9 (VBUS), J1.B4 (VBUS), J1.B9 (VBUS), U2.5 (VP)
col1: MX2.2 (ROW), MX3.1 (COL), MX4.1 (COL), MX5.1 (COL), MX7.1 (COL), MX8.1 (COL), MX9.1 (COL), MX13.1 (COL), MX14.1 (COL), U1.32 (PC7(ICP3/CLK0/OC4A))
col2: MX11.1 (COL), MX12.1 (COL), MX16.1 (COL), MX17.1 (COL), MX18.1 (COL), MX20.1 (COL), MX21.1 (COL), MX22.1 (COL), MX23.1 (COL), U1.25 (PD4(ICP1/ADC8))
col3: MX25.1 (COL), MX26.1 (COL), MX27.1 (COL), MX29.1 (COL), MX30.1 (COL), MX31.1 (COL), MX33.1 (COL), MX35.1 (COL), MX60.1 (COL), U1.22 (PD5(XCLK1/~CTS))
col4: MX34.1 (COL), MX37.1 (COL), MX38.1 (COL), MX39.1 (COL), MX42.1 (COL), MX43.1 (COL), MX44.1 (COL), MX81.1 (COL), MX82.1 (COL), U1.26 (PD6(T1/ADC9/~OC4D))
col5: MX46.1 (COL), MX47.1 (COL), MX48.1 (COL), MX51.1 (COL), MX52.1 (COL), MX55.1 (COL), MX56.1 (COL), MX58.1 (COL), MX61.1 (COL), U1.27 (PD7(T0/OC4D/ADC10))
col6: MX64.1 (COL), MX65.1 (COL), MX66.1 (COL), MX67.1 (COL), MX71.1 (COL), MX74.2 (ROW), MX75.1 (COL), SW2.S2, U1.28 (PB4(PCINT4/ADC11))
row1: D2.1 (K), D7.2 (A), D11.1 (K), D16.2 (A), D25.1 (K), D29.2 (A), D37.1 (K), D42.2 (A), D46.1 (K), D51.2 (A), D63.1 (K), D68.2 (A), U1.20 (PD2(RXD1/INT2))
row2: D3.1 (K), D8.2 (A), D12.1 (K), D20.2 (A), D26.1 (K), D33.2 (A), D38.1 (K), D43.2 (A), D47.1 (K), D55.2 (A), D64.1 (K), D87.2 (A), U1.21 (PD3(TXD1/INT3))
row3: D4.1 (K), D13.2 (A), D17.1 (K), D21.2 (A), D27.1 (K), D30.2 (A), D39.1 (K), D44.2 (A), D56.2 (A), D65.1 (K), U1.29 (PB5(PCINT5/OC1A/ADC12/~OC4B))
row4: D5.1 (K), D18.1 (K), D22.2 (A), D31.1 (K), D34.1 (K), D35.2 (A), D48.1 (K), D52.2 (A), D88.1 (K), U1.30 (PB6(PCINT6/OC1B/OC4B/ADC13))
row5: D9.1 (K), D14.2 (A), D23.1 (K), D40.2 (A), D49.1 (K), D53.2 (A), D58.1 (K), D61.2 (A), D66.1 (K), D70.2 (A), U1.31 (PC6(OC3A/~OC4A))
rpg1: C19.1, SW2.A, U1.18 (PD0(OC0B/SCL/INT0))
rpg2: C20.2, SW2.B, U1.19 (PD1(SDA/INT1))
